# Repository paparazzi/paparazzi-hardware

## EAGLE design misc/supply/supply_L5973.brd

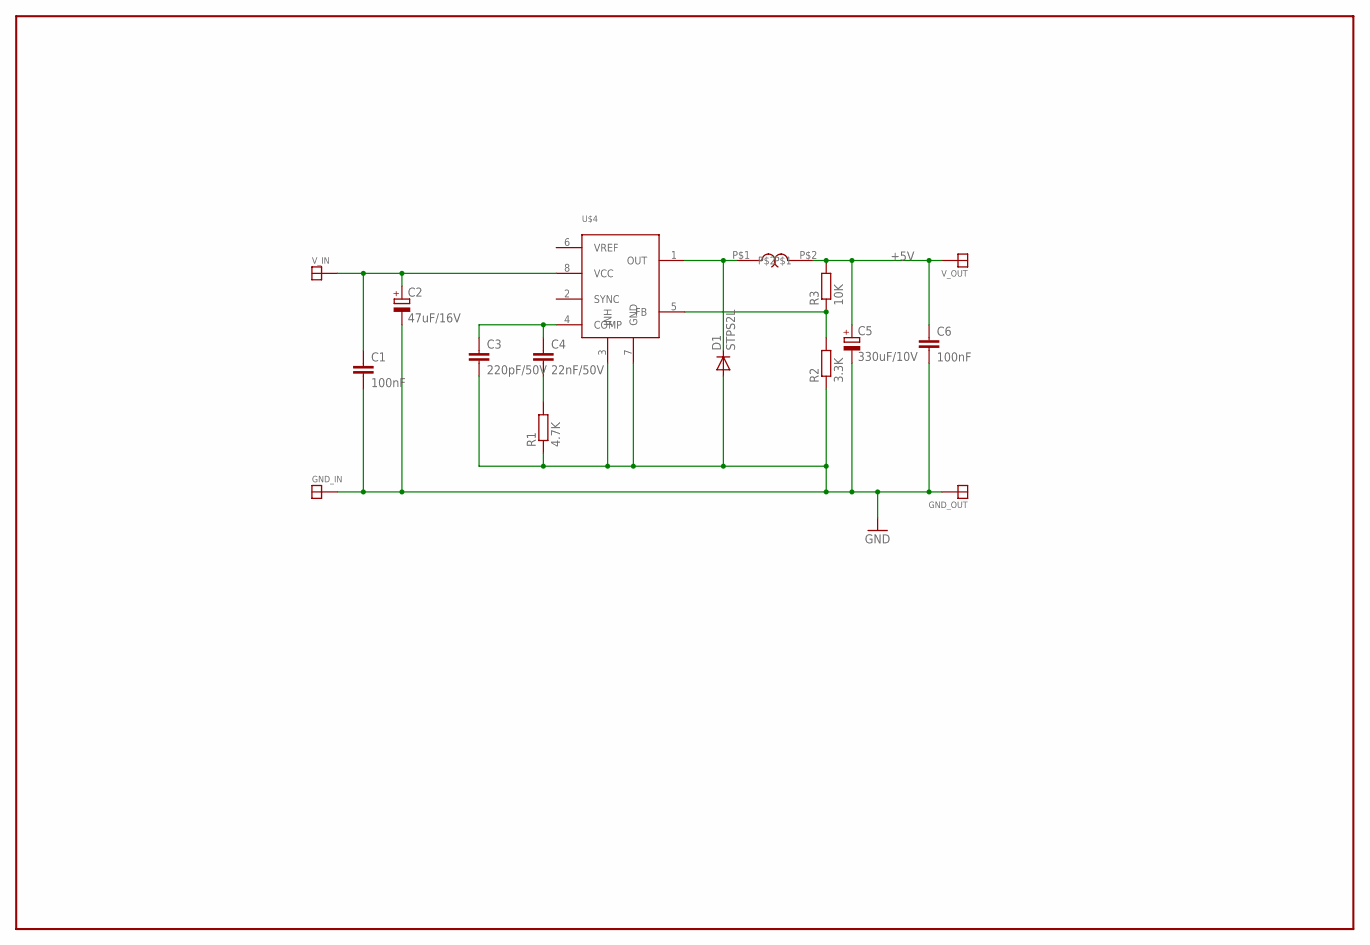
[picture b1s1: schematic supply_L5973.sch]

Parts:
C1, C6: 100nF; C0603
C2: 47uF/16V; D/7343-31R
C3: 220pF/50V; C1206K
C4: 22nF/50V; C1206K
C5: 330uF/10V; D/7343-31R
D1: STPS2L; SMA
GND_IN: SOLDER_PAD100_50; SOLDER_PAD_100_50
GND_OUT: SOLDER_PAD100_50; SOLDER_PAD_100_50
L1: 15uH; WE_PD
R1: 4.7K; R0603
R2: 3.3K; R0603
R3: 10K; R0603
U$4: L5973D; SO08
V_IN: SOLDER_PAD100_50; SOLDER_PAD_100_50
V_OUT: SOLDER_PAD100_50; SOLDER_PAD_100_50

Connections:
+5V: C5.+, C6.1, L1.P$2, R3.2, V_OUT.P$1
GND: C1.2, C2.-, C3.2, C5.-, C6.2, D1.P$1 (A), GND_IN.P$1, GND_OUT.P$1, R1.1, R2.1, U$4.3 (INH), U$4.7 (GND)
unnamed: C3.1, C4.1, U$4.4 (COMP)
unnamed: C4.2, R1.2
unnamed: D1.P$2 (C), L1.P$1, U$4.1 (OUT)
unnamed: R2.2, R3.1, U$4.5 (FB)
VBAT: C1.1, C2.+, U$4.8 (VCC), V_IN.P$1

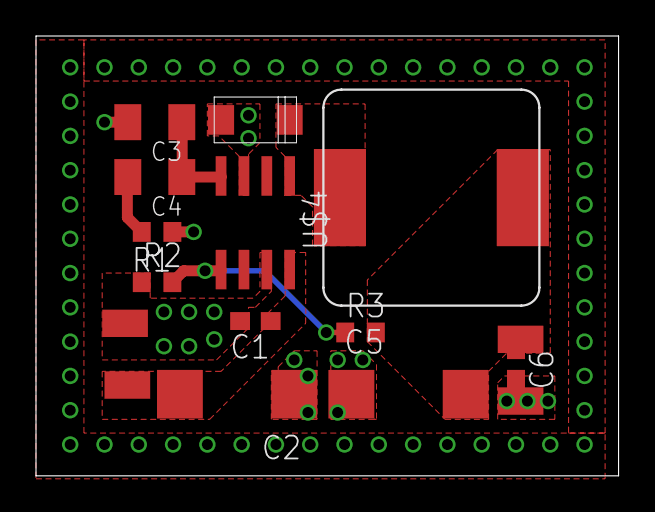
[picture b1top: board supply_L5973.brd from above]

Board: 2 copper layers, 32.4 x 24.4 mm, 16 parts (0 on the bottom side), 7 nets.

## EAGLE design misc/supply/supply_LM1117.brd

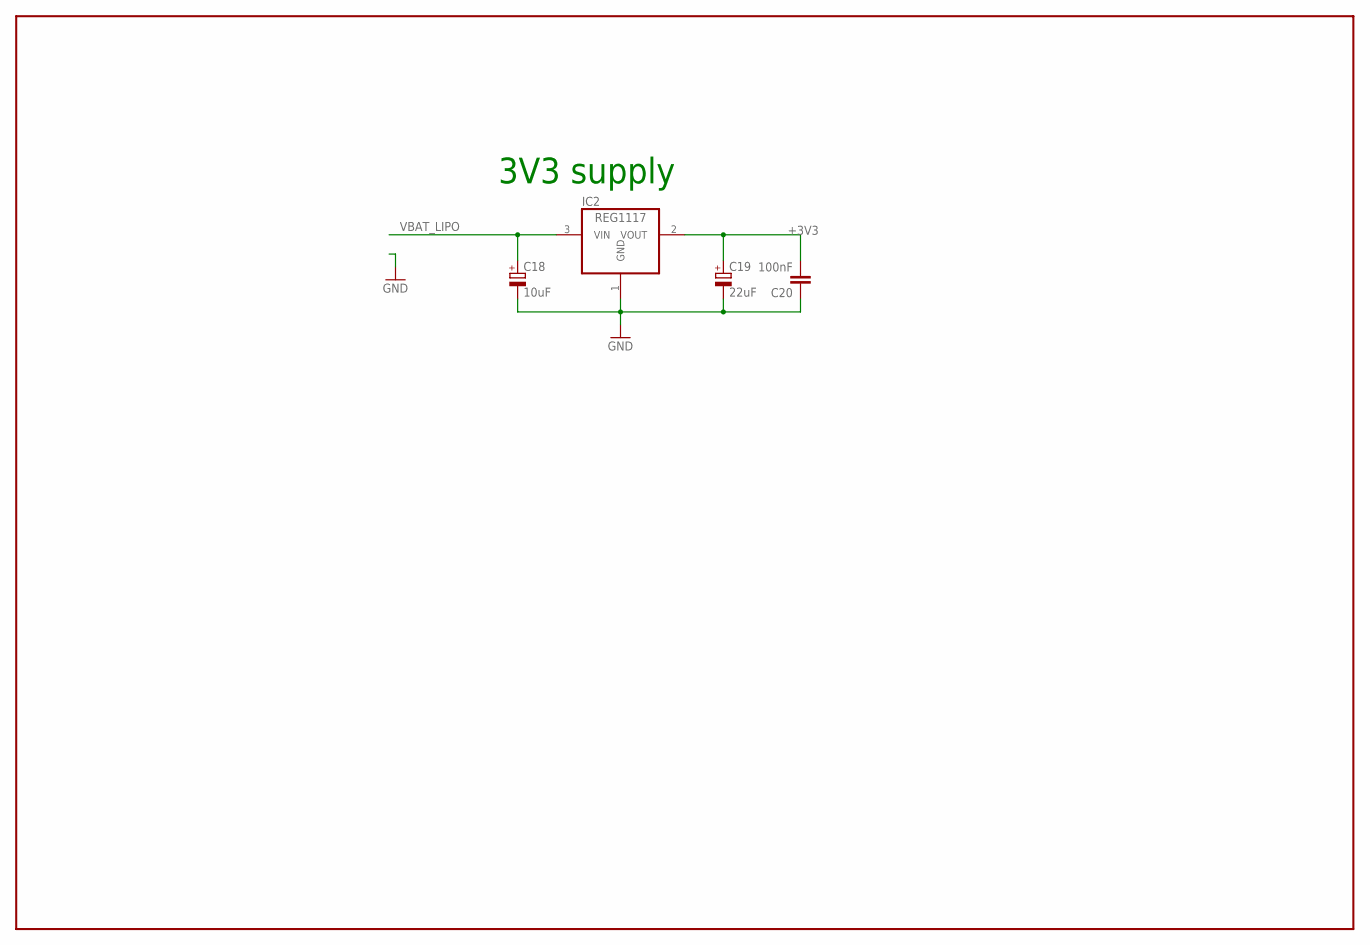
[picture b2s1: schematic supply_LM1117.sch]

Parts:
C18: 10uF; B/3528-21R
C19: 22uF; B/3528-21R
C20: 100nF; C0805K
IC2: REG1117; SOT223

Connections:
+3V3: C19.+, C20.2, IC2.2 (VOUT)
GND: C18.-, C19.-, C20.1, IC2.1 (GND)
VBAT_LIPO: C18.+, IC2.3 (VIN)

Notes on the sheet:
3V3 supply

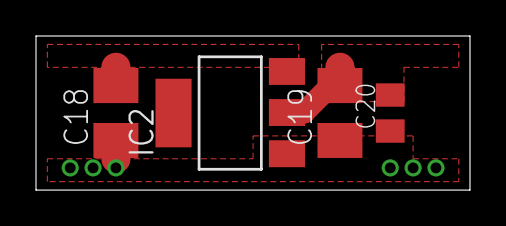
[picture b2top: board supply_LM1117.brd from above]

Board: 4 copper layers, 24.1 x 8.6 mm, 4 parts (0 on the bottom side), 3 nets.

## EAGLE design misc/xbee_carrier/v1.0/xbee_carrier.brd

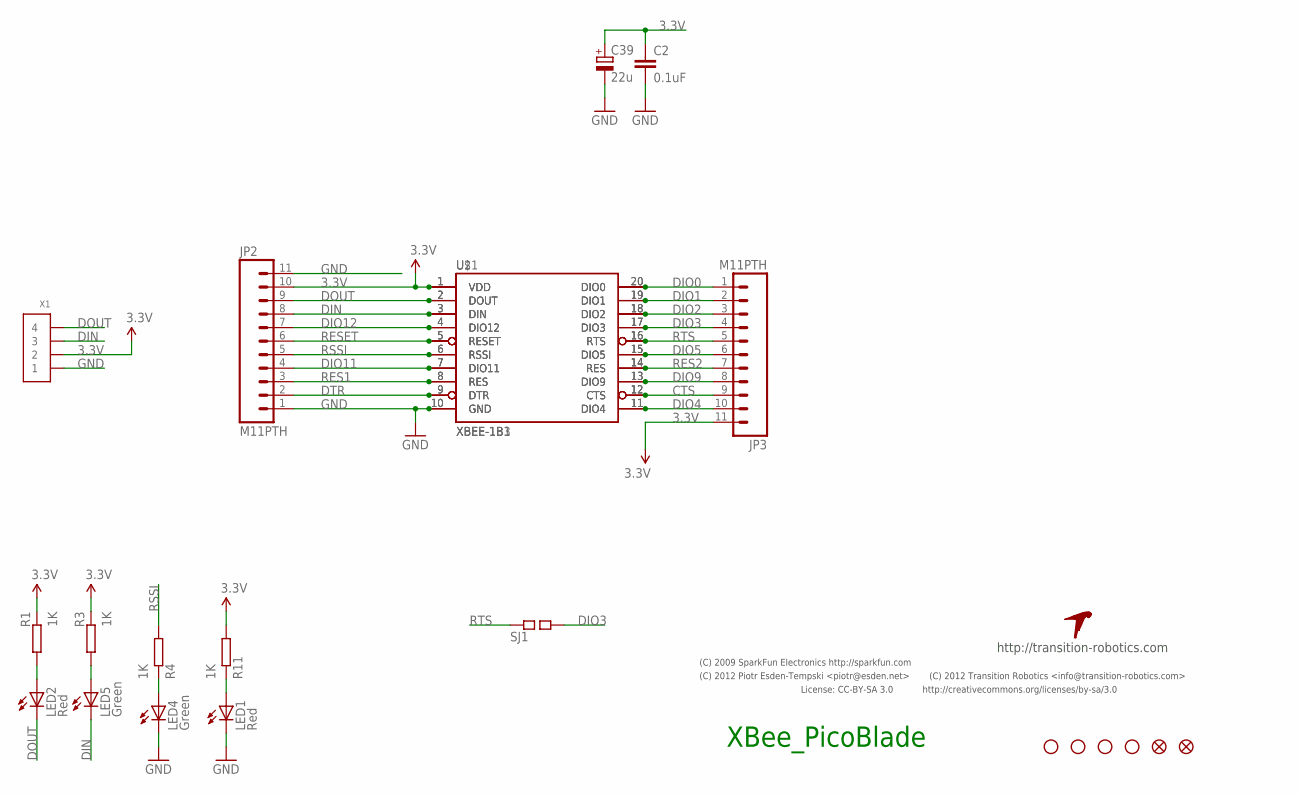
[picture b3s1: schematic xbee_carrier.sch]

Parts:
C2: 0.1uF; 0402-CAP; PARTNO cap-cer-0402-100n
C39: 22u; 3528/B; PARTNO cap-tan-B-22u-16v
JP2, JP3: M11PTH; 1X11; PARTNO *
LED1, LED2: Red; 0402-LED; PARTNO led-0402-red
LED4, LED5: Green; 0402-LED; PARTNO led-0402-green
R1, R3, R4, R11: 1K; 0402-RES; PARTNO res-0402-1k5
SJ1: SQ_JMP-0402; 0402-SQJMP; PARTNO *
U2: XBEE-1B3; XBEE-SMD; PARTNO *
U$1: XBEE-1B1; XBEE-1; PARTNO *
U$2: TR-LOGO; PARTNO *
U$5, U$9, U$10, U$11: STAND-OFF; PARTNO *
U$7, U$16: FIDUCIAL1X2; FIDUCIAL-1X2; PARTNO *
X1: CONN_4-1-53261; PB-53261-04; PARTNO conn-picoblade-smd-0.05in-4

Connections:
3.3V: C2.P$1 (1), C39.+, JP2.10, JP3.11, R1.P$1 (1), R3.P$1 (1), R11.P$2 (2), U2.1 (VDD), U$1.1 (VDD), X1.2
CTS: JP3.9, U2.12 (CTS), U$1.12 (CTS)
DIN: JP2.8, LED5.C, U2.3 (DIN), U$1.3 (DIN), X1.3
DIO0: JP3.1, U2.20 (DIO0), U$1.20 (DIO0)
DIO1: JP3.2, U2.19 (DIO1), U$1.19 (DIO1)
DIO2: JP3.3, U2.18 (DIO2), U$1.18 (DIO2)
DIO3: JP3.4, SJ1.P$2 (2), U2.17 (DIO3), U$1.17 (DIO3)
DIO4: JP3.10, U2.11 (DIO4), U$1.11 (DIO4)
DIO5: JP3.6, U2.15 (DIO5), U$1.15 (DIO5)
DIO9: JP3.8, U2.13 (DIO9), U$1.13 (DIO9)
DIO11: JP2.4, U2.7 (DIO11), U$1.7 (DIO11)
DIO12: JP2.7, U2.4 (DIO12), U$1.4 (DIO12)
DOUT: JP2.9, LED2.C, U2.2 (DOUT), U$1.2 (DOUT), X1.4
DTR: JP2.2, U2.9 (DTR), U$1.9 (DTR)
GND: C2.P$2 (2), C39.-, JP2.1, JP2.11, LED1.C, LED4.C, U2.10 (GND), U$1.10 (GND), X1.1
unnamed: LED2.A, R1.P$2 (2)
unnamed: LED4.A, R4.P$1 (1)
unnamed: LED5.A, R3.P$2 (2)
unnamed: LED1.A, R11.P$1 (1)
RES1: JP2.3, U2.8 (RES), U$1.8 (RES)
RES2: JP3.7, U2.14 (RES), U$1.14 (RES)
RESET: JP2.6, U2.5 (RESET), U$1.5 (RESET)
RSSI: JP2.5, R4.P$2 (2), U2.6 (RSSI), U$1.6 (RSSI)
RTS: JP3.5, SJ1.P$1 (1), U2.16 (RTS), U$1.16 (RTS)

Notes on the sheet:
XBee_PicoBlade
License: CC-BY-SA 3.0
http://creativecommons.org/licenses/by-sa/3.0
(C) 2012 Piotr Esden-Tempski <piotr@esden.net>
(C) 2009 SparkFun Electronics http://sparkfun.com
http://transition-robotics.com
(C) 2012 Transition Robotics <info@transition-robotics.com>

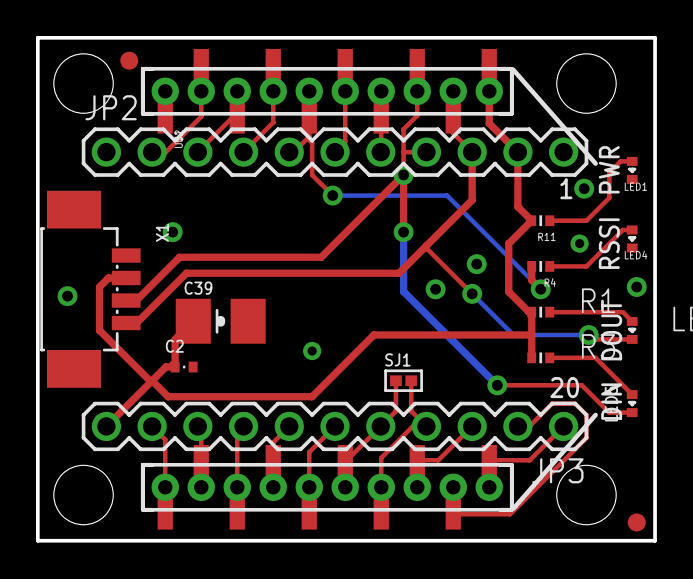
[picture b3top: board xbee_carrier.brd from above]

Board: 2 copper layers, 34.3 x 27.9 mm, 23 parts (1 on the bottom side), 24 nets.

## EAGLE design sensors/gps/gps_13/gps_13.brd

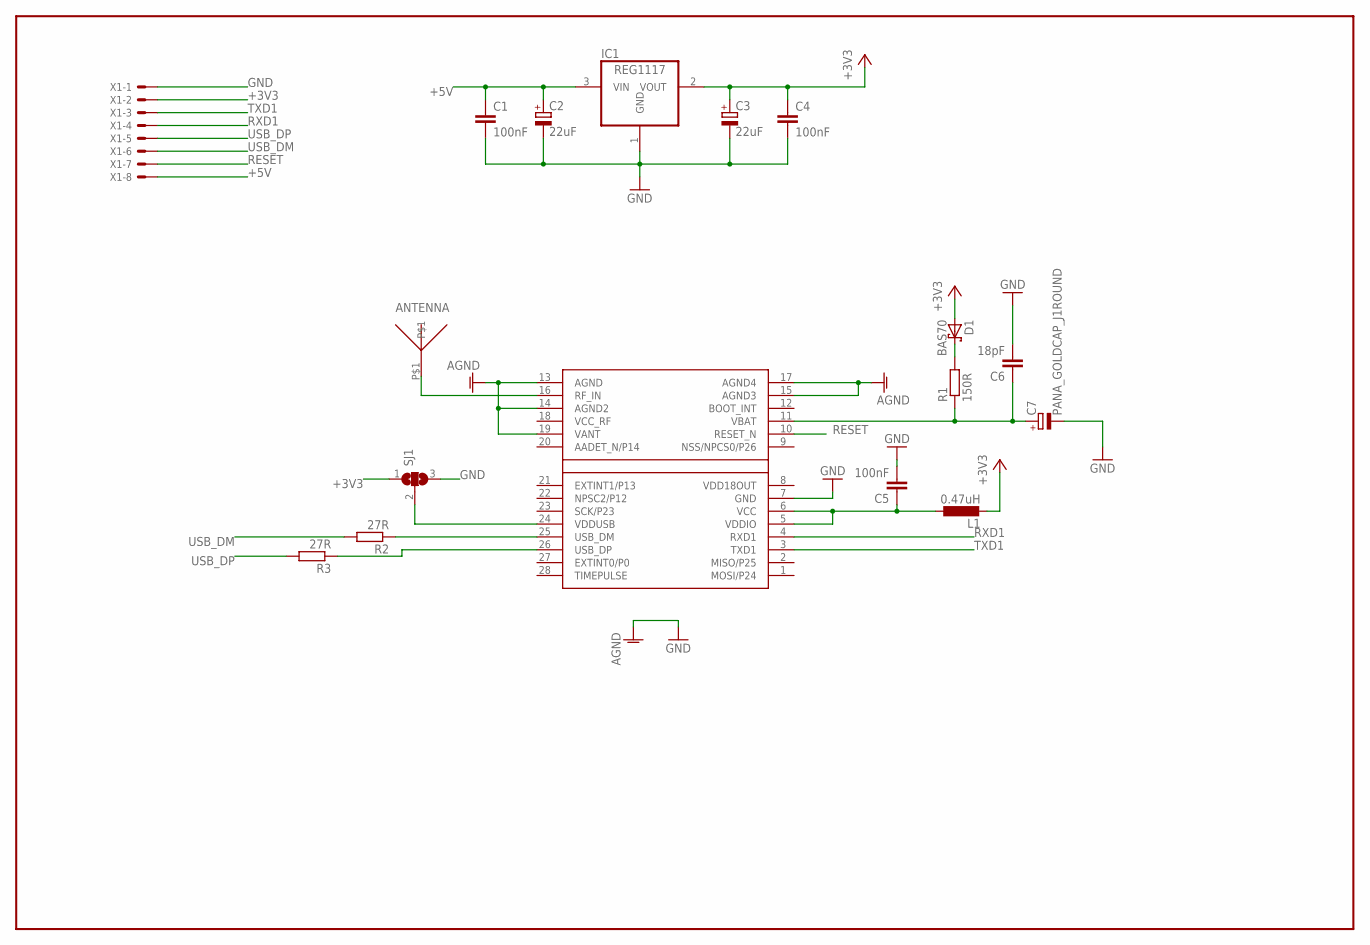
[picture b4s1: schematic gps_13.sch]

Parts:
ANTENNA: GPS_ANT_13
C1, C4, C5: 100nF; C0603K
C2, C3: 22uF; B/3528-21R
C6: 18pF; C0603K
C7: PANA_GOLDCAP_J1ROUND; PANA_J1_BIS
D1: BAS70; SOT23
IC1: REG1117; SOT223
L1: 0.47uH; L2012C
R1: 150R; R1005
R2, R3: 27R; R1005
SJ1: SJ2W; SJ_2
U$6: LEA-4P; LEA-LA
X1: 53047-08

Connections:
+3V3: C3.+, C4.1, D1.1 (A), IC1.2 (VOUT), L1.2, SJ1.1, X1.2
+5V: C1.1, C2.+, IC1.3 (VIN), X1.8
GND: C1.2, C2.-, C3.-, C4.2, C5.2, C6.2, C7.MINUS (-), IC1.1 (GND), SJ1.3, U$6.7 (GND), U$6.13 (AGND), U$6.14 (AGND2), U$6.15 (AGND3), U$6.17 (AGND4), U$6.19 (VANT), X1.1
unnamed: C5.1, L1.1, U$6.5 (VDDIO), U$6.6 (VCC)
unnamed: ANTENNA.P$1, U$6.16 (RF_IN)
unnamed: R2.1, U$6.25 (USB_DM)
unnamed: R3.1, U$6.26 (USB_DP)
unnamed: SJ1.2, U$6.24 (VDDUSB)
unnamed: C6.1, C7.PLUS (+), R1.1, U$6.11 (VBAT)
unnamed: D1.3 (C), R1.2
RESET: U$6.10 (RESET_N), X1.7
RXD1: U$6.4 (RXD1), X1.4
TXD1: U$6.3 (TXD1), X1.3
USB_DM: R2.2, X1.6
USB_DP: R3.2, X1.5
VCC_RF: U$6.18 (VCC_RF)
VDD18OUT: U$6.8 (VDD18OUT)

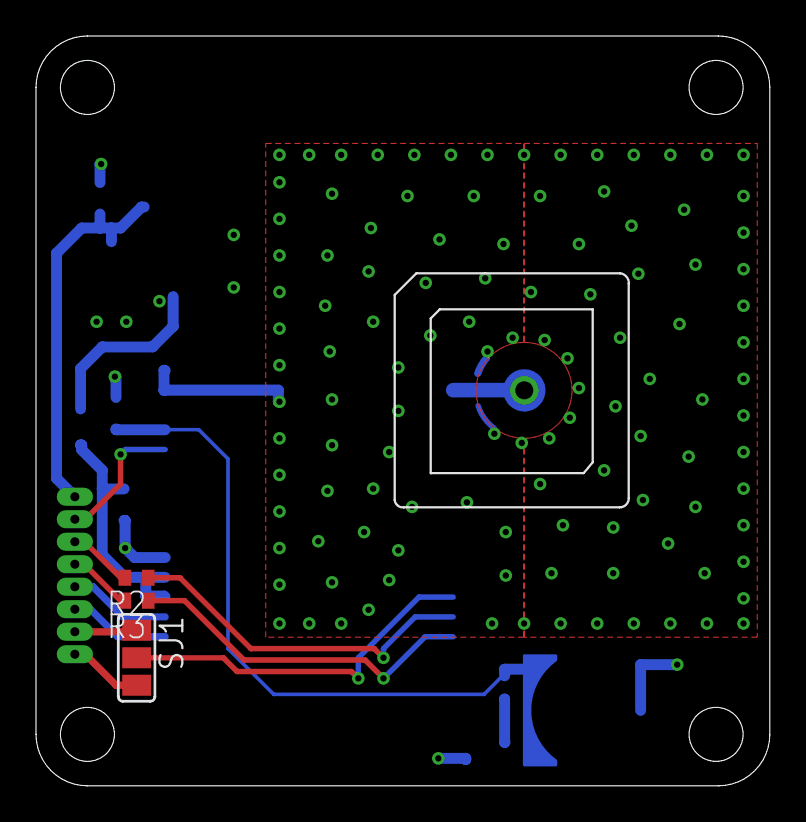
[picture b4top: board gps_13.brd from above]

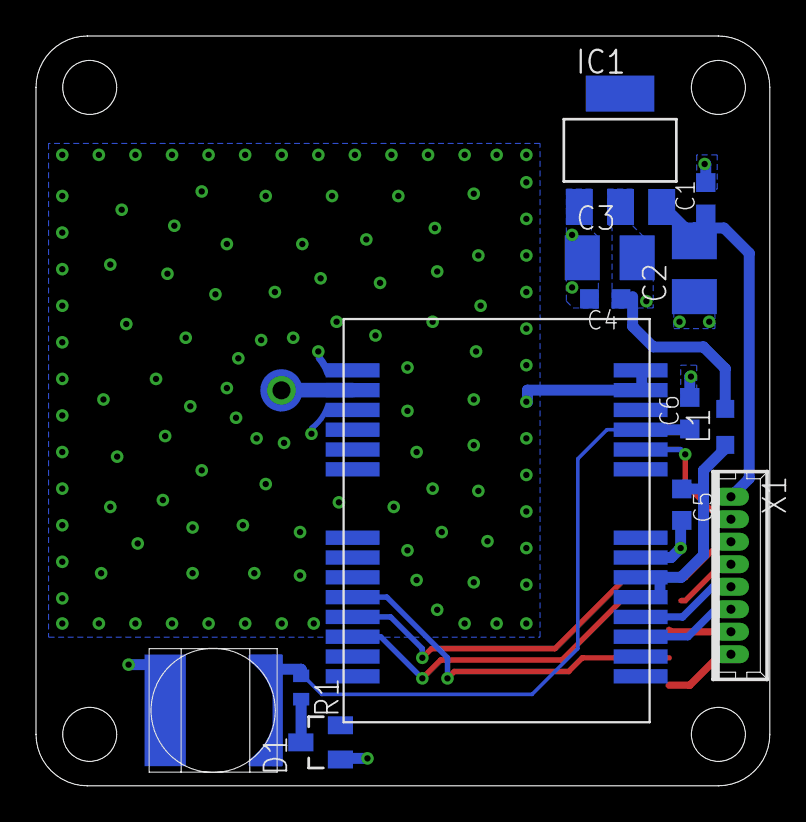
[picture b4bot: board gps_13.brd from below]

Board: 4 copper layers, 40.8 x 41.7 mm, 17 parts (13 on the bottom side), 15 nets.

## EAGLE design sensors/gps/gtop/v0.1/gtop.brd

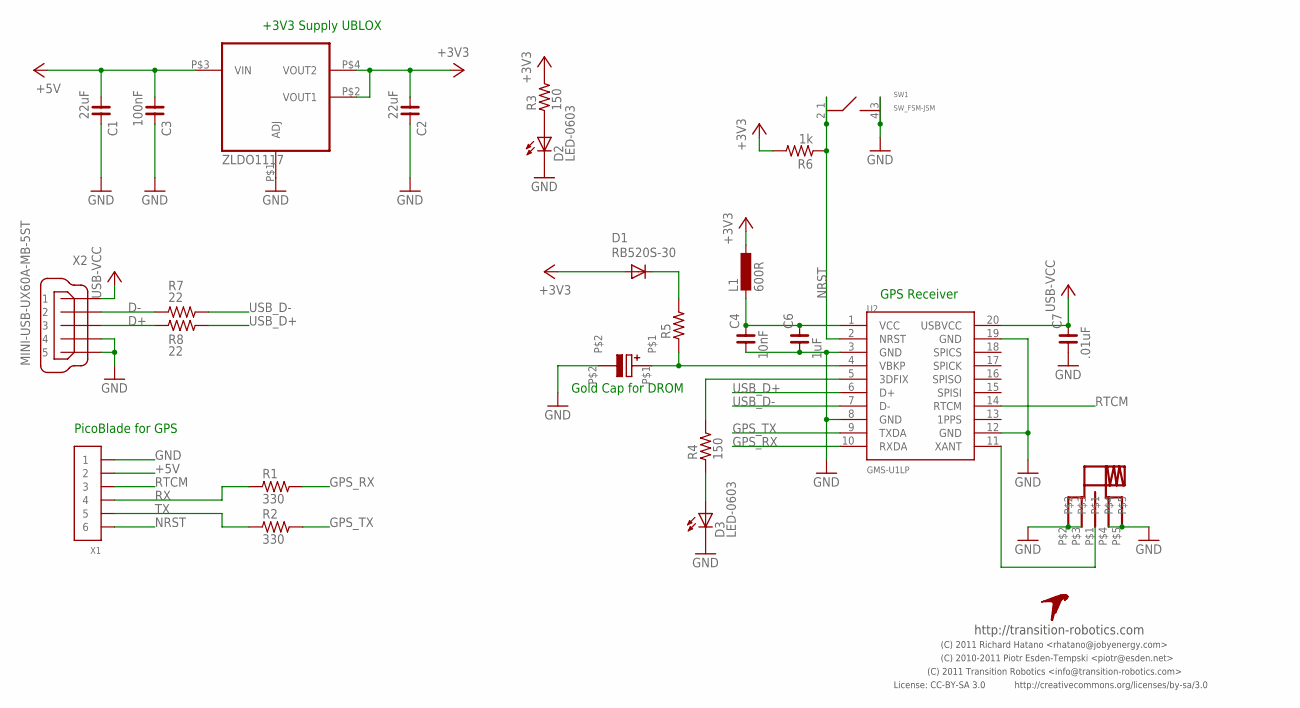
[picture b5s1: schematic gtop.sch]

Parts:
C1, C2: 22uF; C0805
C3: 100nF; C0805
C4: 10nF; C0603
C5: EECEN0F204AK
C6: 1uF; C0603
C7: .01uF; C0603
D1: RB520S-30; SOD523-DIO
D2, D3: LED-0603; 0603-LED
J1: JOBY_ROBOTICS_SMA
L1: 600R; 0603-IND
R1, R2: 330; R0603
R3, R4: 150; R0603
R5: R_0603; R0603
R6: 1k; R0603
R7, R8: 22; R0603
SW1: SW_FSM-JSM; SW-FSM_JSM
U1: ZLDO1117
U2: GMS-U1LP
U$3: TR-LOGO; PARTNO *
X1: CONN_6-1-53261; PB-53261-06
X2: MINI-USB-UX60A-MB-5ST; UX60A-MB-5ST

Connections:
+3V3: C2.1, D1.2 (A), L1.P$1 (1), R3.2, R6.2, U1.P$2 (VOUT1), U1.P$4 (VOUT2)
+5V: C1.1, C3.1, U1.P$3 (VIN), X1.2
D+: R8.1, X2.3
D-: R7.1, X2.2
GND: C1.2, C2.2, C3.2, C4.1, C5.P$2, C6.1, C7.1, D2.C, D3.C, J1.P$2, J1.P$3, J1.P$4, J1.P$5, SW1.3, SW1.4, U1.P$1 (ADJ), U2.3 (GND), U2.8 (GND), U2.12 (GND), U2.19 (GND), X1.1, X2.4, X2.5
GPS_RX: R1.2, U2.10 (RXDA)
GPS_TX: R2.2, U2.9 (TXDA)
unnamed: J1.P$1, U2.11 (XANT)
unnamed: R4.2, U2.5 (3DFIX)
unnamed: D1.1 (C), R5.2
unnamed: C5.P$1, R5.1, U2.4 (VBKP)
unnamed: C4.2, C6.2, L1.P$2 (2), U2.1 (VCC)
unnamed: D3.A, R4.1
unnamed: D2.A, R3.1
NRST: R6.1, SW1.1, SW1.2, U2.2 (NRST), X1.6
RTCM: U2.14 (RTCM), X1.3
RX: R1.1, X1.4
TX: R2.1, X1.5
USB-VCC: C7.2, U2.20 (USBVCC), X2.1
USB_D+: R8.2, U2.6 (D+)
USB_D-: R7.2, U2.7 (D-)

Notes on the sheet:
GPS Receiver
PicoBlade for GPS
Gold Cap for DROM
+3V3 Supply UBLOX
http://transition-robotics.com
License: CC-BY-SA 3.0
http://creativecommons.org/licenses/by-sa/3.0
(C) 2010-2011 Piotr Esden-Tempski <piotr@esden.net>
(C) 2011 Richard Hatano <rhatano@jobyenergy.com>
(C) 2011 Transition Robotics <info@transition-robotics.com>

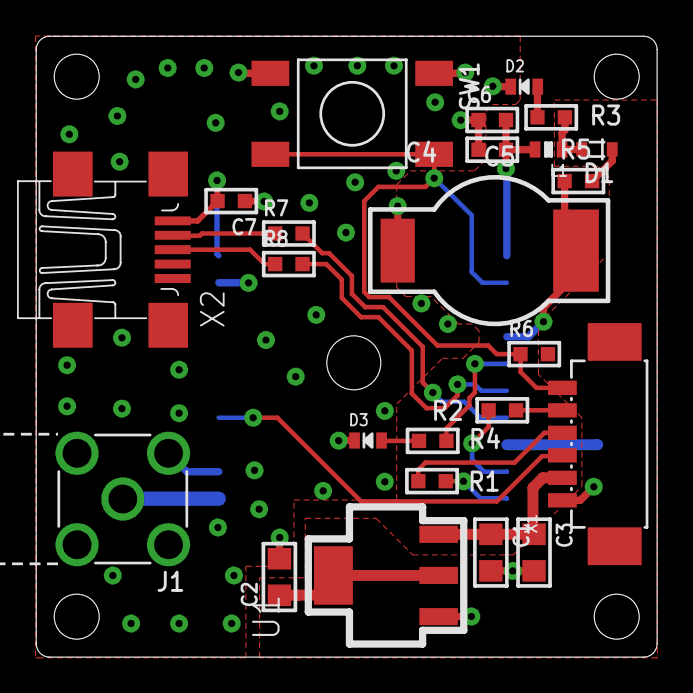
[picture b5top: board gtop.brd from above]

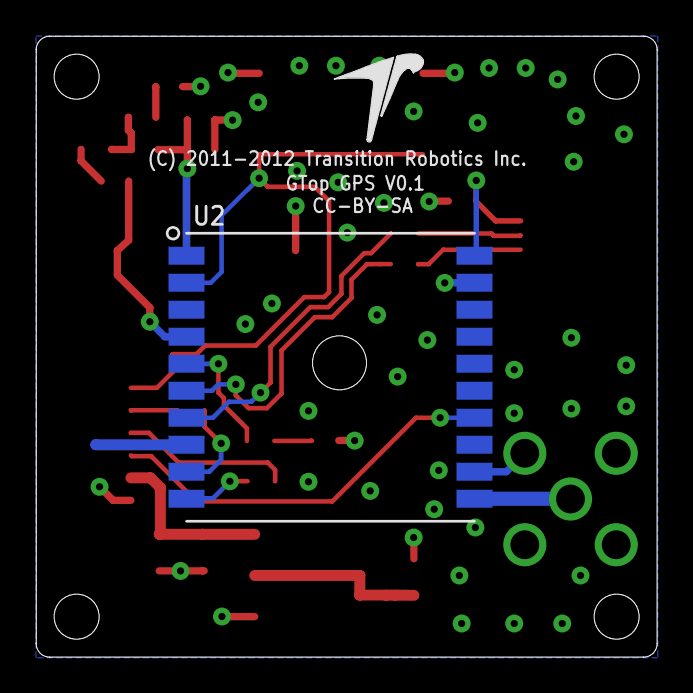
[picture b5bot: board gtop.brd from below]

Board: 2 copper layers, 34.5 x 34.5 mm, 26 parts (2 on the bottom side), 21 nets.

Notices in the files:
misc/xbee_carrier/v1.0/xbee_carrier.brd:
CC-BY-SA V3.0
sensors/gps/gtop/v0.1/gtop.brd:
Licensed under:
(C) 2010-2012 Piotr Esden-Tempski
(C) 2011-2012 Transition Robotics
(C) 2011-2012 Transition Robotics Inc.
parts and their libraries:
SparkFun-RF: Licensing: CC v3.0 Share-Alike You are welcome to use this library for commercial purposes.
